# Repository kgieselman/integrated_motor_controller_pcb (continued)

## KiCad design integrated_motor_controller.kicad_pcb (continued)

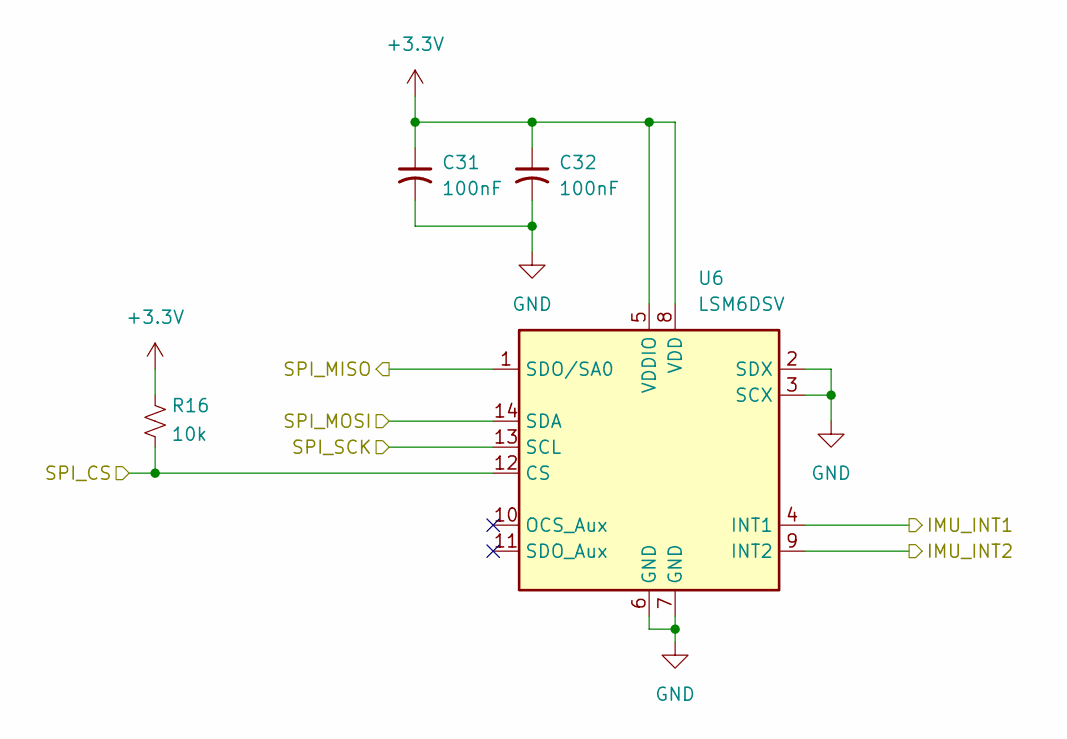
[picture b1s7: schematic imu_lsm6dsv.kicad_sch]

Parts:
C31, C32: 100nF; C_0603_1608Metric; Part No CC0603KRX7R9BB104; JLCPCB C14663
R16: 10k; R_0603_1608Metric; Part No 0603WAF1002T5E; JLCPCB C25804
U6: LSM6DSV; LGA-14_3x2.5mm_P0.5mm_LayoutBorder3x4y; JLCPCB C41785564

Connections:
/IMU/IMU_INT1: U6.4 (INT1); also elsewhere on the board
/IMU/IMU_INT2: U6.9 (INT2); also elsewhere on the board
/IMU/SPI_CS: R16.2, U6.12 (CS); also elsewhere on the board
/IMU/SPI_MISO: U6.1 (SDO/SA0); also elsewhere on the board
/IMU/SPI_MOSI: U6.14 (SDA); also elsewhere on the board
/IMU/SPI_SCK: U6.13 (SCL); also elsewhere on the board

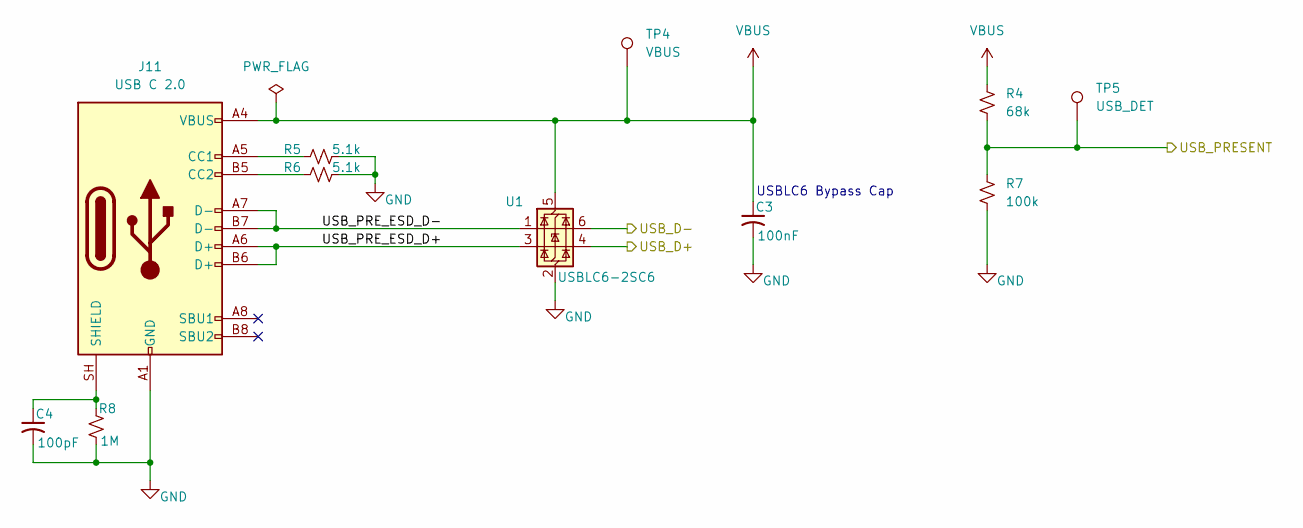
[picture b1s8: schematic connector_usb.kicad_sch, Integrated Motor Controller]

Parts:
C3: 100nF; C_0603_1608Metric; Part No CC0603KRX7R9BB104; JLCPCB C14663
C4: 100pF; C_0603_1608Metric; Part No CL10C101JB8NNNC; JLCPCB C14858
J11: USB C 2.0; USB_C_Receptacle_HRO_TYPE-C-31-M-12; Part No TYPE-C-31-M-12; JLCPCB C165948
R4: 68k; R_0603_1608Metric; Part No 0603WAF6802T5E; JLCPCB C23231
R5, R6: 5.1k; R_0603_1608Metric; Part No 0603WAF5101T5E; JLCPCB C23186
R7: 100k; R_0603_1608Metric; Part No 0603WAF1003T5E; JLCPCB C25803
R8: 1M; R_0603_1608Metric; Part No 0603WAF1004T5E; JLCPCB C22935
TP4: VBUS; TestPoint_Pad_D1.0mm; Part No ---; JLCPCB ---
TP5: USB_DET; TestPoint_Pad_D1.0mm; Part No ---; JLCPCB ---
U1: USBLC6-2SC6; SOT-23-6; Part No USBLC6-2SC6; JLCPCB C7519

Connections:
/Microcontroller/USB_D+: U1.4 (I/O2); also elsewhere on the board
/Microcontroller/USB_D-: U1.6 (I/O1); also elsewhere on the board
/Microcontroller/USB_PRESENT: R4.2, R7.1, TP5.1 (1_1); also elsewhere on the board
/USB Connector/USB_PRE_ESD_D+: J11.A6 (D+), J11.B6 (D+), U1.3 (I/O2)
/USB Connector/USB_PRE_ESD_D-: J11.A7 (D-), J11.B7 (D-), U1.1 (I/O1)
unnamed: J11.A5 (CC1), R5.1
unnamed: J11.B5 (CC2), R6.1
unnamed: C4.1, J11.SH (SHIELD), R8.1
VBUS: C3.1, J11.A4 (VBUS), J11.A9 (VBUS), J11.B4 (VBUS), J11.B9 (VBUS), R4.1, TP4.1 (1_1), U1.5 (VBUS); also elsewhere on the board

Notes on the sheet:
USBLC6 Bypass Cap

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
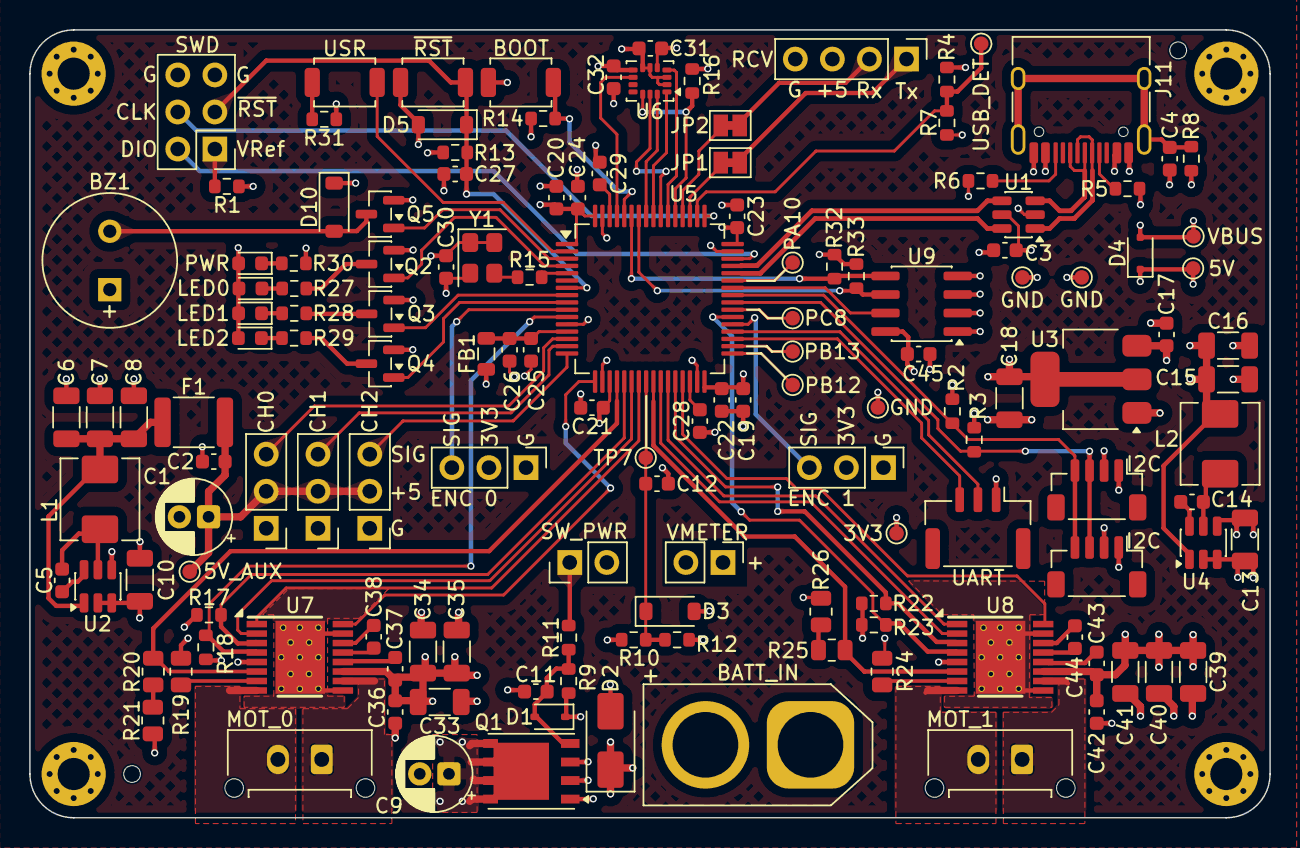
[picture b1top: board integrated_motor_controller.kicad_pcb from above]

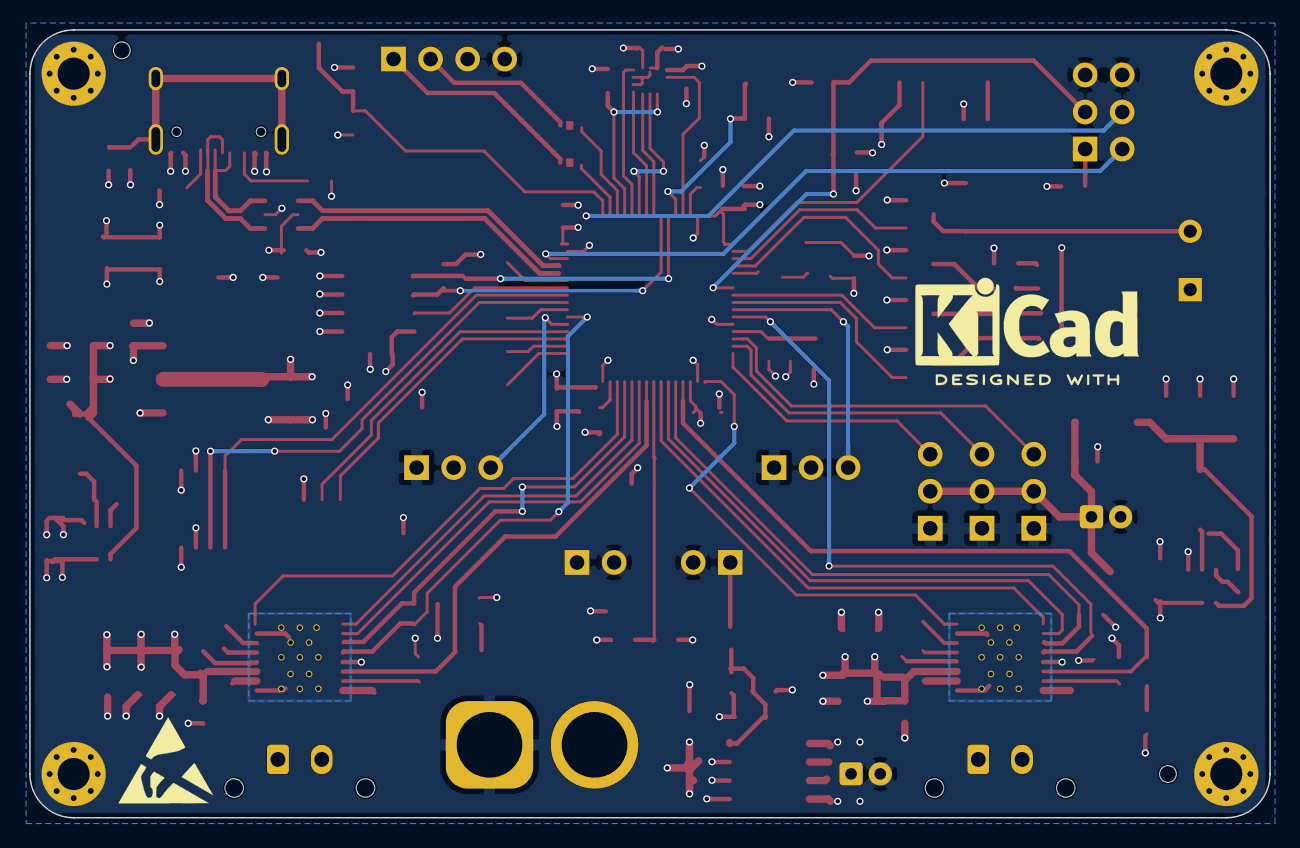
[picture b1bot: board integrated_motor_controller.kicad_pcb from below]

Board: 4 copper layers, 85.0 x 54.0 mm, 150 parts (2 on the bottom side), 99 nets.

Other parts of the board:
C45: 100nF; C_0603_1608Metric
R32, R33: 3.3k; R_0603_1608Metric

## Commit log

2026-05-10 Initial commit of the project files
2026-05-10 Cleanup a comment in main schematic for the new project name
2026-05-11 Final edits before sending to fab
2026-05-11 Update readme now that version 1 has been ordered
2026-05-12 Add comment on main sch for the mating connectors for I2C and UART
